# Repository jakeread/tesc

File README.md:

# FOCT v0.3
### Field Oriented Control on a Teensy 3.2

## Briefly
FOCT does closed-loop control of brushless dc (BLDC) motors: the type normally found in RC Cars, Airplanes, Drones etc. These motors are incredibly power-dense, making them an excellent candidate for Robotics applications. However, it's very difficult to control them at low speeds and in small position intervals. 

FOCT implements 'all the bells and whistles' found in high-end robotics motor controllers (encoder feedback, BEMF & current sensing, etc) in a relatively low-cost solution. Code is written in Arduino for the Teensy Microcontroller, and is meant to be easily extensible and pick-through-able.

FOCT is in development! So is it's documentation!

## The Hardware  
FOCT uses a Teensy 3.2 to control Three H-Bridges, which each drive one phase of a three-phase brushless motor. The H-Bridge gates are driven with a DRV8302, a wunderkid IC that is also home to a 5V Buck Converter (for your peripheral needs) and two differential Op-Amps, used to measure phase current. The board also has simple voltage-dividers connected to Teensy ADCs for measuring phase voltage, and includes an SPI out connector used to interface with an AS5047 encoder for absolute position sensing. For now, input is done over Teensy's blazing-fast serial port.  
  
Up to ~24v supply  
Up to 30A without a heatsink, 42 with good cooling, peaks of 60  
Planned PWM in, SPI slave modes for control. Serial over USB Config / testing.  

## The Software
FOCT runs on Arduino! It uses Teensy's built interval timers to handle fast-loop-insurance, and only occasionally reaches into the chip's registers to make PWM work properly. Code will be well commented, I hope / promise...

## How it Works: Closed-Loop BLDC Control
// 6-step commutation w/ position reference

## How it Works: Field-Oriented Control
// FOC ! Transforms, current measurement, UVW || AB || IQ frames  

## TBD's, software
- Proper filtering on Current measurement, encoder measurement  
- Tuning the FOC loop  
- Encoder Offset Discovery routine  
- Auto Tuning, interface, system integration, oh my

## TBD's, hardware
- ADC voltage divider to sense VBUS voltage
- More DAC outputs / testing pins so to tune FOC
- SMD Thermistor near the FETS ?  
- Go to STM32F4 & chibios ?
- Caps could be closer to FETS, heatsink strap

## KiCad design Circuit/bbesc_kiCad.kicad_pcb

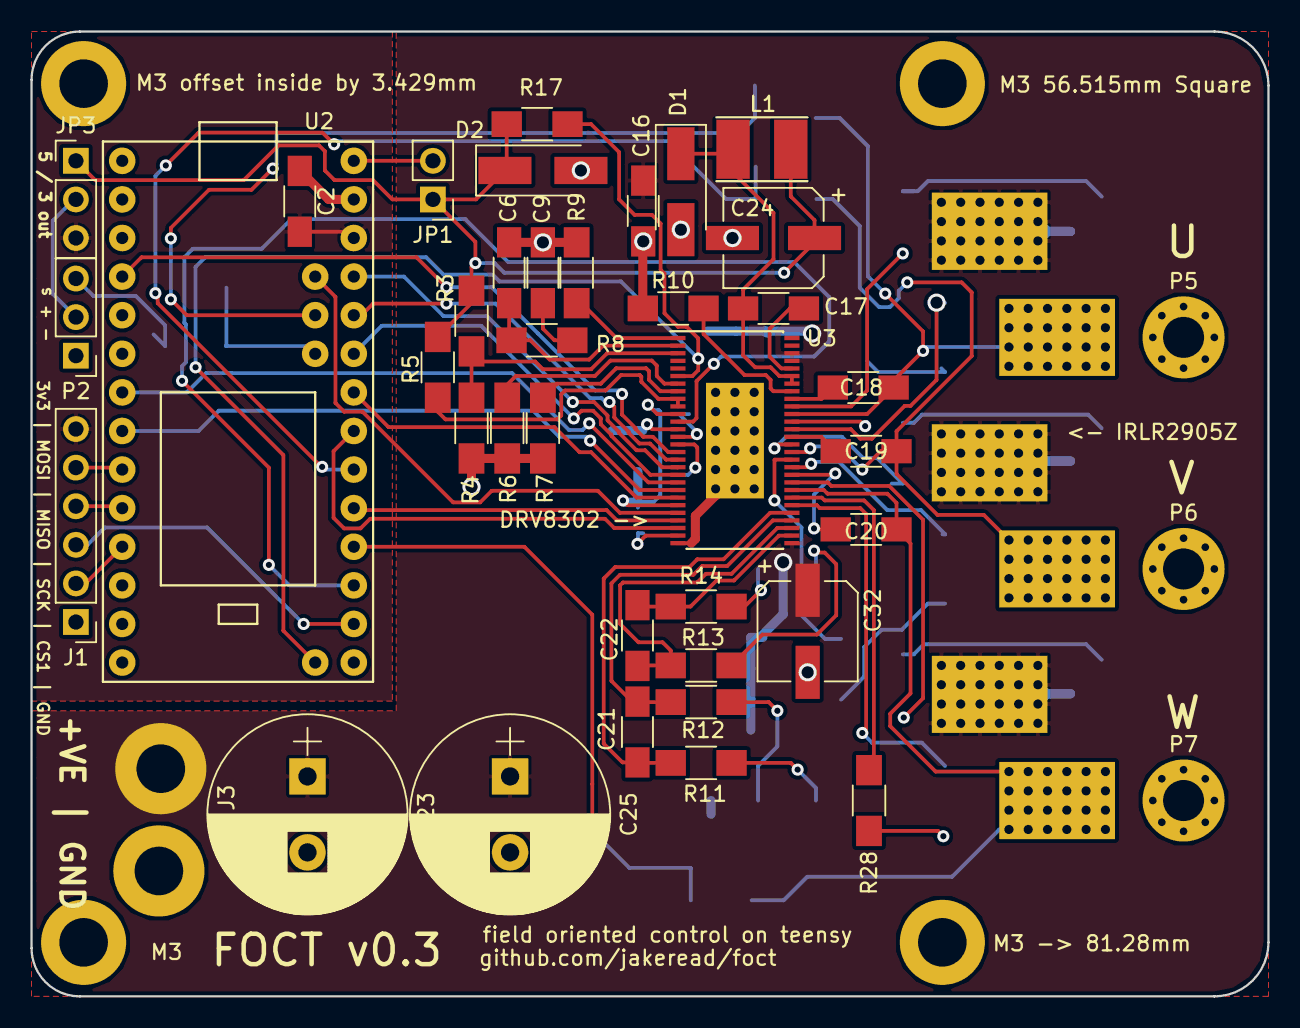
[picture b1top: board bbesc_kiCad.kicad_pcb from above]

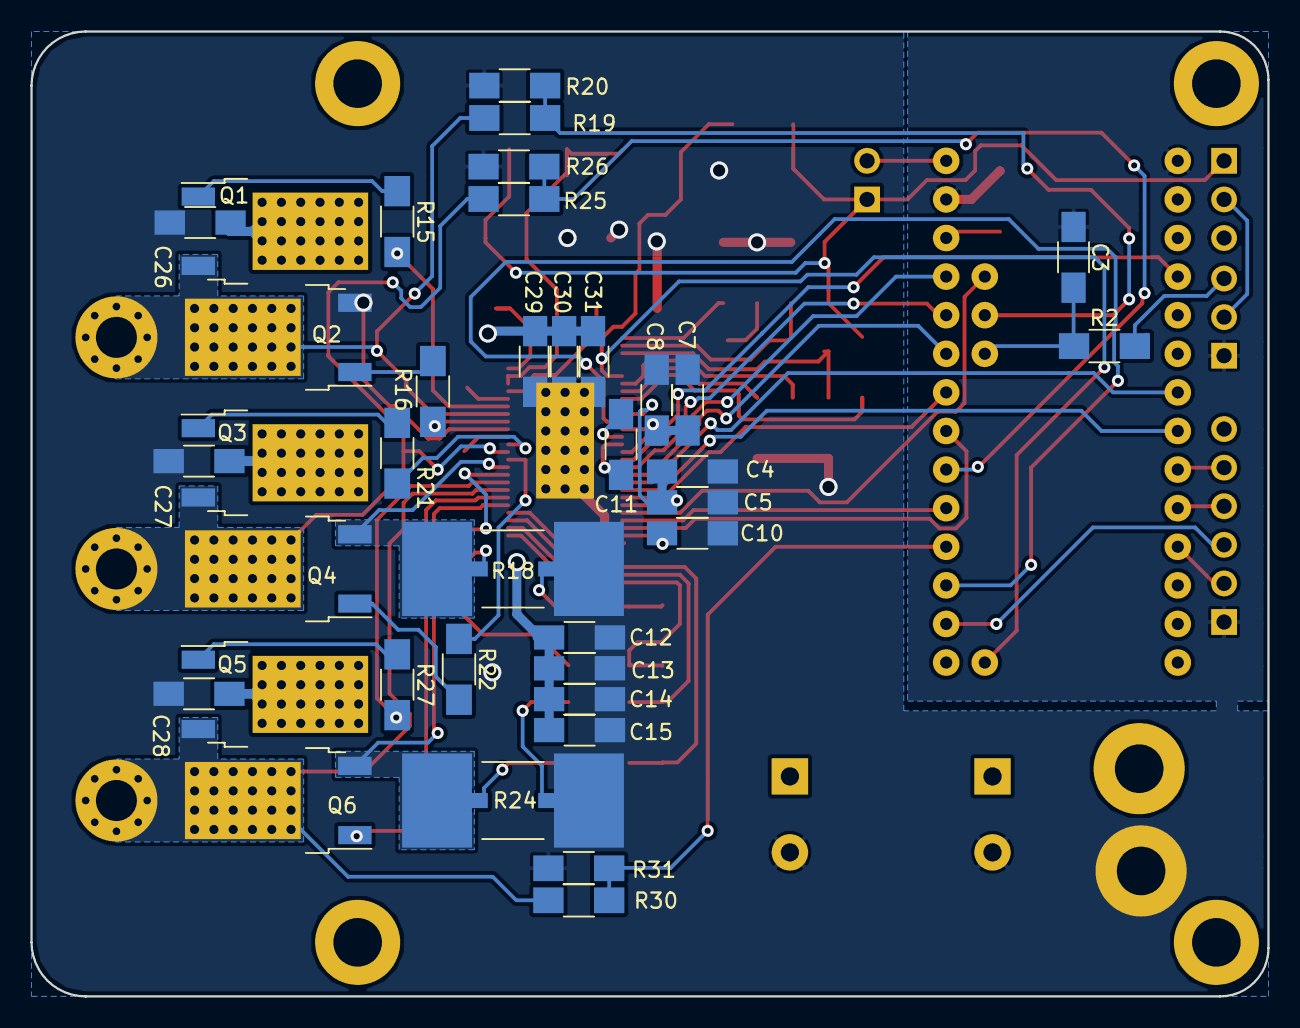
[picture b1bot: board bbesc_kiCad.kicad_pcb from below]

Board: 2 copper layers, 81.4 x 63.5 mm, 82 parts (37 on the bottom side), 70 nets.

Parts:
C2, C3, C13, C14, C16, C26, C27, C28, C29, C30, C31: 10uF; C_1206_HandSoldering
C4, C5, C7, C8, C10: 2.2uF; C_1206_HandSoldering
C6: 120pF; C_1206_HandSoldering
C9: 6.8nF; C_1206_HandSoldering
C11: 22nF; C_1206_HandSoldering
C12: 1uF; C_1206_HandSoldering
C15: 15uF; C_1206_HandSoldering
C17: 100nF; C_1206_HandSoldering
C18, C19, C20: 220nF; C_1206_HandSoldering
C21, C22: 2.2nF; C_1206_HandSoldering
C23, C25: 2000uF; CP_Radial_D13.0mm_P5.00mm
C24, C32: 100uF; CP_Elec_6.3x7.7
D1: DIODESCH; D_SMA_Handsoldering
D2: TVS 5v; D_SMA_Handsoldering
J1: CONN_01X06; Pin_Header_Straight_1x06_Pitch2.54mm
J3: CONN_01X02; WireConnection_2.50mmDrill_LargePad
JP1: JUMPER; Pin_Header_Straight_1x02_Pitch2.54mm
JP3: JUMPER3; Pin_Header_Straight_1x03_Pitch2.54mm
L1: 22uH; Inductor_Taiyo-Yuden_NR-40xx_HandSoldering
M3, M3 56.515mm Square, M3 -> 81.28mm, M3 offset inside by 3.429mm: MountingHole_3.2mm_M3_DIN965_Pad
P2: CONN_01X03; Pin_Header_Straight_1x03_Pitch2.54mm
P5, P6, P7: CONN_01X01; MountingHole_2.7mm_Pad_Via
Q1, Q2, Q3, Q4, Q5, Q6: Q_NMOS_GDS; TO-252-2
R2: 47R; R_1206_HandSoldering
R3: 18k; R_1206_HandSoldering
R4, R6, R7: 3k3; R_1206_HandSoldering
R5, R17: 10k; R_1206_HandSoldering
R8: 15k; R_1206_HandSoldering
R9: 220k; R_1206_HandSoldering
R10: 1M; R_1206_HandSoldering
R11, R12, R13, R14: 100R; R_1206_HandSoldering
R15, R16, R21, R22, R27, R28: 4R7; R_1206_HandSoldering
R18, R24: SHNT; R_SHUNT_3920
R19, R25, R30: 39K; R_1206_HandSoldering
R20, R26, R31: 5K6; R_1206_HandSoldering
U2: teensy_3-2; Teensy3.2-bottomLess
U3: DRV_8302; TSSOP-56_6.1x14mm_Pitch0.5mm

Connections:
3v3: C2.2, J1.6, JP3.3, U2.24
5v: C24.1, D2.1, JP1.1, JP3.1, L1.1, R3.2, R5.2, R17.1
/H_V_LO: Q4.3, R18.1, U3.39
/H_W_LO: Q6.3, R24.1, U3.34
/SHNT_V_HI: R13.1, R18.3
/SHNT_V_LO: R14.1, R18.4
/SHNT_W_HI: R11.1, R24.3
/SHNT_W_LO: R12.1, R24.4
A_SENS_U: U2.17, U3.25
A_SENS_V: U2.19, U3.26
CS2: J1.2, U2.9
DC_CAL: U2.15, U3.12
DRV_FAULT: R17.2, U2.28, U3.6
DRV_HI_U: R15.2, U3.47
DRV_HI_V: R21.2, U3.42
DRV_HI_W: R27.2, U3.37
DRV_LO_U: R16.2, U3.45
DRV_LO_V: R22.2, U3.40
DRV_LO_W: R28.2, U3.35
EN_GATE: U2.2, U3.16
GND: C2.1, C3.1, C4.2, C5.2, C6.2, C7.2, C8.2, C9.2, C10.2, C12.2, C13.2, C14.2, C15.2, C16.1, C23.2, C24.2, C25.2, C26.2, C27.2, C28.2, C29.2, C30.2, C31.2, C32.2, D1.2, D2.2, J1.1, J3.1, P2.1, Q2.3, R4.1, R6.1, R7.1, R9.2, R10.1, R18.2, R20.2, R24.2, R26.2, R31.2, U2.25, U2.27, U3.28, U3.44, U3.57
MC_AREF: U2.31, U3.24
MC_HI_U: U2.22, U3.17
MC_HI_V: U2.21, U3.19
MC_HI_W: U2.6, U3.21
MC_LO_U: U2.23, U3.18
MC_LO_V: U2.5, U3.20
MC_LO_W: U2.20, U3.22
MISO2: J1.4, U2.8
MOSI2: J1.5, U2.7
unnamed: C4.1, C5.1, U3.11, U3.23
unnamed: C6.1, R8.1, U3.2
unnamed: C7.1, C8.1, U3.13
unnamed: C9.1, R8.2
unnamed: C10.1, U3.27
unnamed: C11.1, U3.14
unnamed: C11.2, U3.15
unnamed: C17.1, D1.1, L1.2, U3.50, U3.51
unnamed: C17.2, U3.52
unnamed: C18.2, U3.48
unnamed: C19.2, U3.43
unnamed: C20.2, U3.38
unnamed: C21.1, R12.2, U3.32
unnamed: C21.2, R11.2, U3.33
unnamed: C22.1, R14.2, U3.30
unnamed: C22.2, R13.2, U3.31
unnamed: JP1.2, U2.26
unnamed: JP3.2, P2.2
unnamed: P2.3, R2.2
unnamed: Q1.1, R15.1
unnamed: Q2.1, R16.1
unnamed: Q3.1, R21.1
unnamed: Q4.1, R22.1
unnamed: Q5.1, R27.1
unnamed: Q6.1, R28.1
unnamed: R3.1, R4.2, U3.3
unnamed: R5.1, U3.9, U3.10
unnamed: R6.2, U3.7
unnamed: R7.2, U3.8
unnamed: R9.1, U3.1
unnamed: R10.2, U3.49
PHASE_U: C18.1, P5.1, Q1.3, Q2.2, R19.1, U3.46
PHASE_V: C19.1, P6.1, Q3.3, Q4.2, R25.1, U3.41
PHASE_W: C20.1, P7.1, Q5.3, Q6.2, R30.1, U3.36
SCK2: J1.3, U2.14
SIMPLE_INPUT: C3.2, R2.1, U2.29
VCC: C12.1, C13.1, C14.1, C15.1, C16.2, C23.1, C25.1, C26.1, C27.1, C28.1, C29.1, C30.1, C31.1, C32.1, J3.2, Q1.2, Q3.2, Q5.2, U3.29, U3.53, U3.54
V_SENS_U: R19.2, R20.1, U2.30
V_SENS_V: R25.2, R26.1, U2.18
V_SENS_W: R30.2, R31.1, U2.16

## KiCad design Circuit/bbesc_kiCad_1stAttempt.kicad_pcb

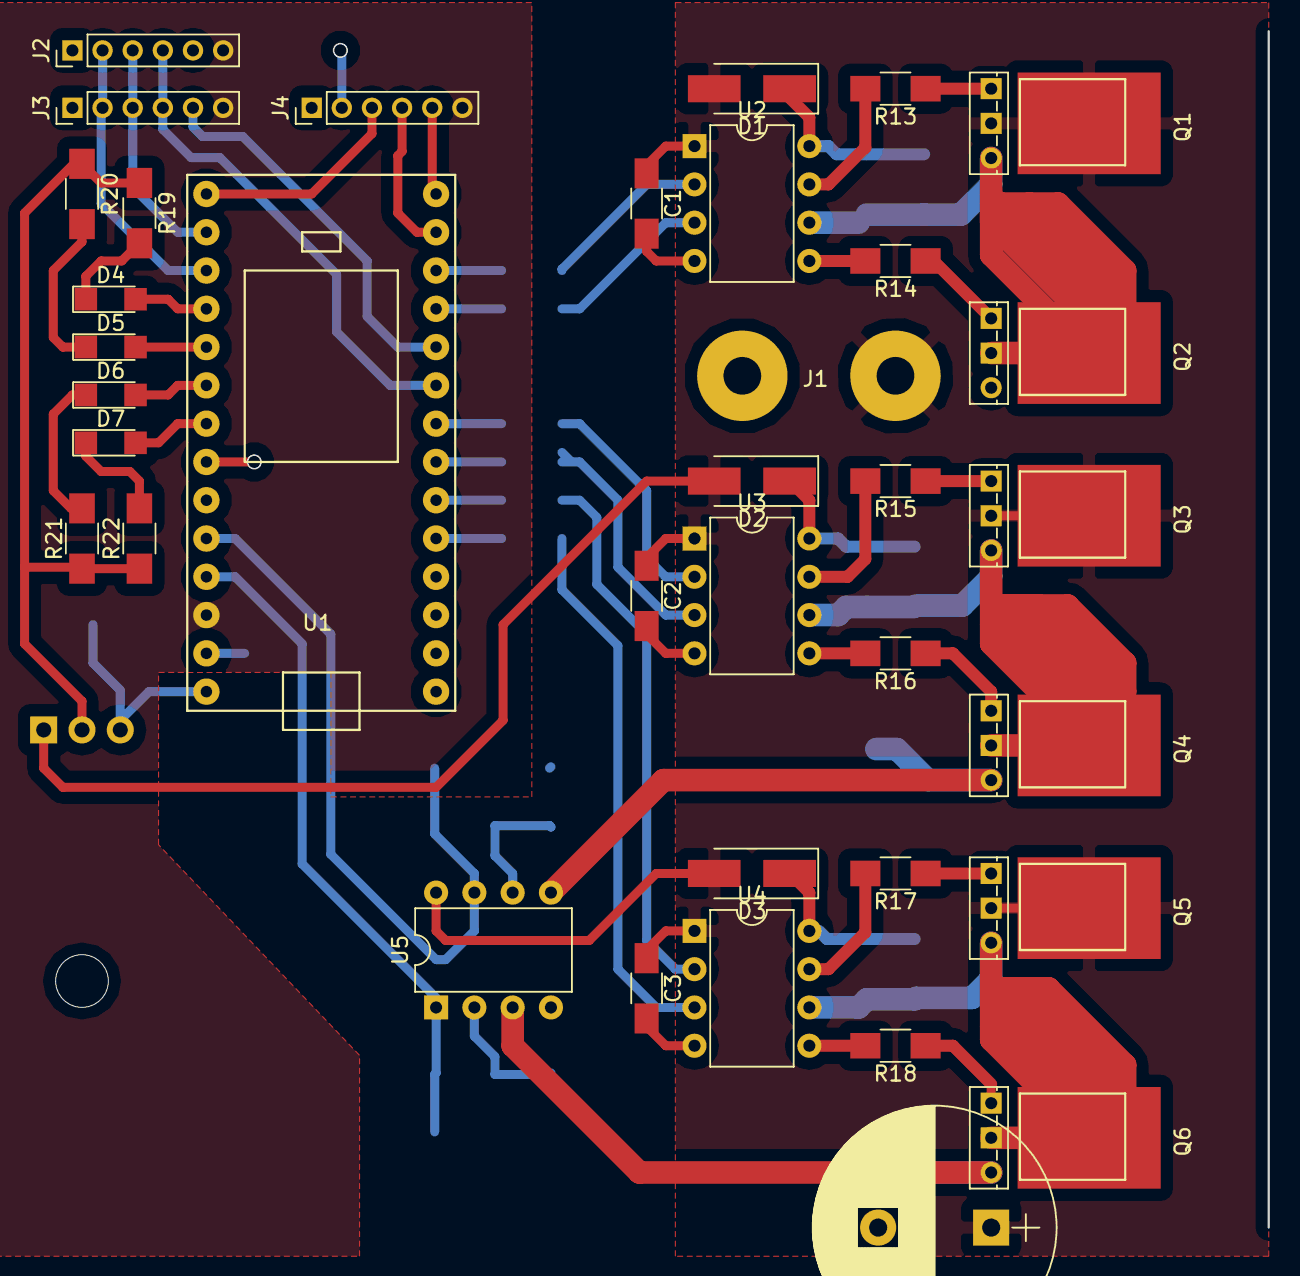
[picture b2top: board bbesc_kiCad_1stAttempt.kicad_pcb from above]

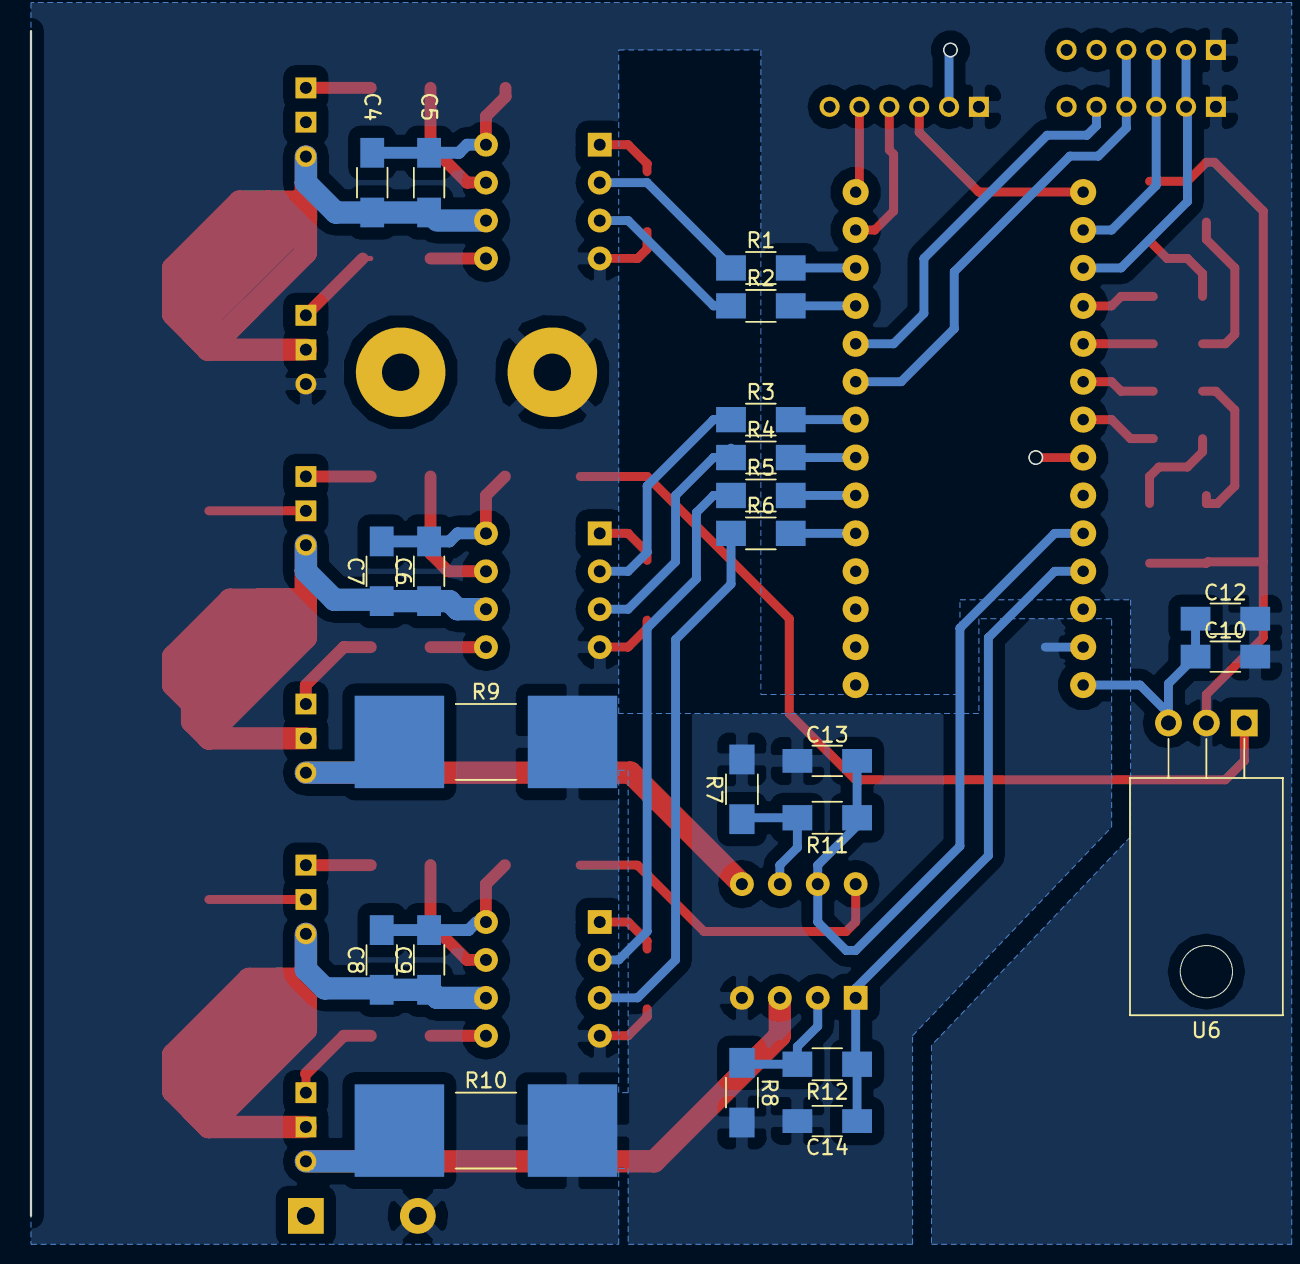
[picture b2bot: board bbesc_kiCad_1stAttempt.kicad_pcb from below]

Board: 2 copper layers, 59 parts (23 on the bottom side), 56 nets.

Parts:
C1, C2, C3, C10, C12: 1uF; C_1206_HandSoldering
C4, C6, C8: 10uF; C_1206_HandSoldering
C5, C7, C9, C13, C14: 0.1uF; C_1206_HandSoldering
C11: 2000uF; CP_Radial_D16.0mm_P7.50mm
D1, D2, D3: 1N4001; D_SMA_Handsoldering
D4, D5, D6, D7: LED; LED_1206
J1: CONN_01X02; WireConnection_2.50mmDrill_LargePad
J2, J3, J4: CONN_01X06; Pin_Header_Straight_1x06_Pitch2.00mm
Q1, Q2, Q3, Q4, Q5, Q6: Q_NMOS_GDS; TO-251_IPAK_Vertical
R1, R2, R3, R4, R5, R6: 470R; R_1206_HandSoldering
R7, R8: 12k; R_1206_HandSoldering
R9, R10: .001; R_2816_HandSoldering
R11, R12: 470k; R_1206_HandSoldering
R13, R14, R15, R16, R17, R18: 47R; R_1206_HandSoldering
R19, R20, R21, R22: 4K7; R_1206_HandSoldering
U1: teensy_3-2; Teensy3.2-bottomLess
U2, U3, U4: IR2101; DIP-8_W7.62mm
U5: LM358N; DIP-8_W7.62mm
U6: LM7805; TO-220_Horizontal

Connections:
3v3: J2.6, J3.6, J4.6, U1.24
CS1: J4.2, U1.20
CS2: J2.2, J3.2, U1.15
GND: C1.2, C2.2, C3.2, C10.2, C11.2, C12.2, C13.1, C14.2, J1.1, J2.1, J3.1, J4.1, Q2.3, R7.2, R8.2, R9.2, R10.2, R19.1, R20.1, R21.1, R22.1, U1.25, U1.27, U2.4, U3.4, U4.4, U5.4, U6.2
MISO1: J4.5, U1.12
MISO2: J3.5, U1.8
MOSI1: J4.4, U1.11
MOSI2: J2.4, J3.4, U1.7
unnamed: C4.1, C5.1, Q1.3, Q2.2, U2.6
unnamed: C4.2, C5.2, D1.1, U2.8
unnamed: C6.1, C7.1, Q3.3, Q4.2, U3.6
unnamed: C6.2, C7.2, D2.1, U3.8
unnamed: C8.1, C9.1, Q5.3, Q6.2, U4.6
unnamed: C8.2, C9.2, D3.1, U4.8
unnamed: C10.1, C12.1, U1.26, U6.3
unnamed: C13.2, R11.1, U1.22, U5.7
unnamed: C14.1, R12.1, U1.23, U5.1
unnamed: D4.1, R19.2
unnamed: D4.2, U1.16
unnamed: D5.1, R20.2
unnamed: D5.2, U1.17
unnamed: D6.1, R21.2
unnamed: D6.2, U1.18
unnamed: D7.1, R22.2
unnamed: D7.2, U1.19
unnamed: Q1.1, R13.1
unnamed: Q2.1, R14.1
unnamed: Q3.1, R15.1
unnamed: Q4.1, R16.1
unnamed: Q4.3, R9.1, U5.5
unnamed: Q5.1, R17.1
unnamed: Q6.1, R18.1
unnamed: Q6.3, R10.1, U5.3
unnamed: R1.1, U2.2
unnamed: R1.2, U1.10
unnamed: R2.1, U2.3
unnamed: R2.2, U1.9
unnamed: R3.1, U3.2
unnamed: R3.2, U1.6
unnamed: R4.1, U3.3
unnamed: R4.2, U1.5
unnamed: R5.1, U4.2
unnamed: R5.2, U1.4
unnamed: R6.1, U4.3
unnamed: R6.2, U1.3
unnamed: R7.1, R11.2, U5.6
unnamed: R8.1, R12.2, U5.2
unnamed: R13.2, U2.7
unnamed: R14.2, U2.5
unnamed: R15.2, U3.7
unnamed: R16.2, U3.5
unnamed: R17.2, U4.7
unnamed: R18.2, U4.5
SCK1: J4.3, U1.13
SCK2: J2.3, J3.3, U1.14
VCC: C1.1, C2.1, C3.1, C11.1, D1.2, D2.2, D3.2, J1.2, Q1.2, Q3.2, Q5.2, U2.1, U3.1, U4.1, U5.8, U6.1

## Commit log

2017-06-12 forked from bbesc
2017-06-30 kernel architecture sketch, bones of serial interpreter, streaming functions
2017-07-02 adding scratchpad, begins work on shell and shell integration
2017-07-02 very important message
2017-07-09 start sampler work, encoder settings discovery script, etc
2017-07-11 add roboscpd, add pwm coordination examples, sketch
2017-07-13 figuring timer registers for pwm and adc coordination
2017-07-14 registers! adc and pwm coordination
2017-07-16 mupload
2017-07-18 circuit for fab, foc bones
2017-07-27 circuit fab files v0.1
2017-07-28 pre santiago
2017-08-11 premerge
2017-08-18 board v0.2
2017-08-22 documentation
2017-08-22 adding img
2017-08-22 docudraft
2017-08-26 closed (encoder) loop 'voltage foc' with sinusoid pwm (discovered svpwm errors)
2017-08-27 rolling first PI loop :|
2017-08-28 commentary on FOC code, cleanup of Kernel
